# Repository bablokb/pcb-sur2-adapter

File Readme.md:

Small Adapter from JST-SUR (2pin) to Pin-Header
===============================================

This is a small adapter for Lego lighting kits that use
JST-SUR connectors.

You can add a PH2, XH2.54-2 or 2-pin DuPont socket/header.

Schematic
---------

Layout
------

3D-View
-------

Note: there is no 3D-file for the SUR-Adapter, so this part
is missing in this image:

License
-------

[![CC BY-SA 4.0][cc-by-sa-shield]][cc-by-sa]

This work is licensed under a
[Creative Commons Attribution-ShareAlike 4.0 International
License][cc-by-sa].

[![CC BY-SA 4.0][cc-by-sa-image]][cc-by-sa]

[cc-by-sa]: http://creativecommons.org/licenses/by-sa/4.0/
[cc-by-sa-image]: https://licensebuttons.net/l/by-sa/4.0/88x31.png
[cc-by-sa-shield]:
https://img.shields.io/badge/License-CC%20BY--SA%204.0-lightgrey.svg

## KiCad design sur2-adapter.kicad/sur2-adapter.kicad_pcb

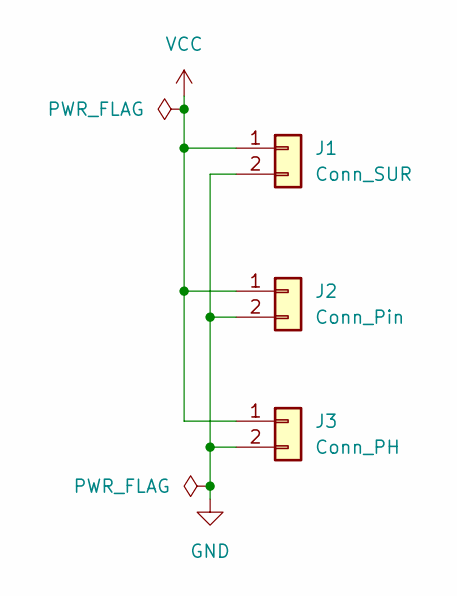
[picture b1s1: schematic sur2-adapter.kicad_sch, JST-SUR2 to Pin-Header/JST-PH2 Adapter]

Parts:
J1: Conn_SUR; JST_SUR_BM02B-SURS-TF_1x02-1MP_P0.80mm_Vertical; LCSC C385130
J2: Conn_Pin; PinHeader_1x02_P2.54mm_Vertical
J3: Conn_PH; JST_PH_S2B-PH-SM4-TB_1x02-1MP_P2.00mm_Horizontal

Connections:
GND: J1.2, J2.2, J3.2
VCC: J1.1, J2.1, J3.1

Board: 2 copper layers, 3 parts (1 on the bottom side), 2 nets, no tracks yet.

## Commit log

2025-07-03 Rev. 1.00 final version in production
2025-07-19 add images
